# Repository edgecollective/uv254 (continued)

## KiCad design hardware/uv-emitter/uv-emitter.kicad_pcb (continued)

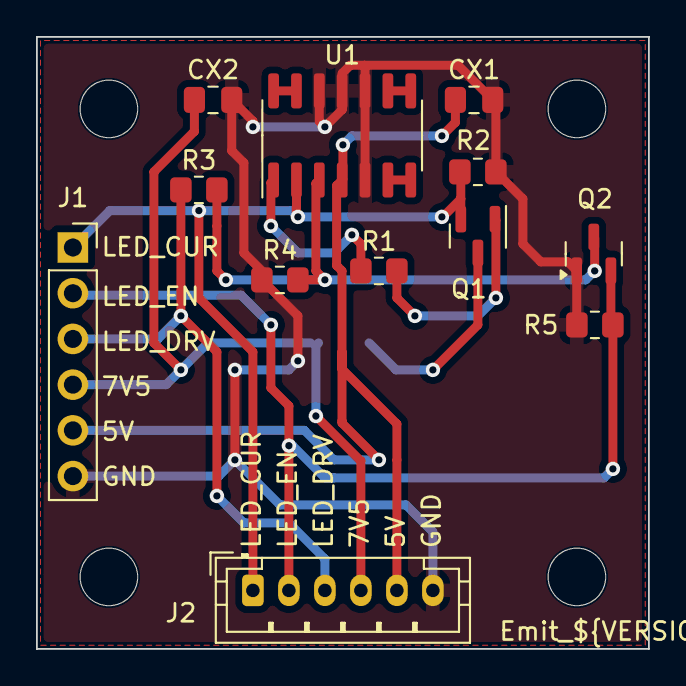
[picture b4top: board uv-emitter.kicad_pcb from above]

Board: 2 copper layers, 34.0 x 34.0 mm, 17 parts (1 on the bottom side), 13 nets.

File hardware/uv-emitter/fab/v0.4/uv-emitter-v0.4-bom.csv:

"Refs","Value","Footprint","Qty","DNP","Description"
"CX1","0.1 uF","Capacitor_SMD:C_0805_2012Metric_Pad1.18x1.45mm_HandSolder","1","","Unpolarized capacitor"
"CX2","1 uF","Capacitor_SMD:C_0805_2012Metric_Pad1.18x1.45mm_HandSolder","1","","Unpolarized capacitor"
"D1","UV LED","uv254:LED_IN-C35PPCTGU0","1","",""
"H1,H2,H3,H4","MountingHole","MountingHole:MountingHole_3.2mm_M3","4","","Mounting Hole without connection"
"J1","Conn_01x06_Socket","Connector_PinSocket_2.54mm:PinSocket_1x06_P2.54mm_Vertical","1","","Generic connector, single row, 01x06, script generated"
"J2","Conn_01x06_Socket","Connector_JST:JST_PH_B6B-PH-K_1x06_P2.00mm_Vertical","1","","Generic connector, single row, 01x06, script generated"
"Q1,Q2","2N7000","Package_TO_SOT_SMD:SOT-23","2","","0.2A Id, 200V Vds, N-Channel MOSFET, 2.6V Logic Level, TO-92"
"R1","49.9","Resistor_SMD:R_0805_2012Metric_Pad1.20x1.40mm_HandSolder","1","",""
"R2","24.9","Resistor_SMD:R_0805_2012Metric_Pad1.20x1.40mm_HandSolder","1","",""
"R3","100K","Resistor_SMD:R_0805_2012Metric_Pad1.20x1.40mm_HandSolder","1","",""
"R4","24.9K","Resistor_SMD:R_0805_2012Metric_Pad1.20x1.40mm_HandSolder","1","",""
"R5","10K","Resistor_SMD:R_0805_2012Metric_Pad1.20x1.40mm_HandSolder","1","",""
"U1","OPA4340UA","Package_SO:SOIC-14_3.9x8.7mm_P1.27mm","1","","Quad Single-Supply, Rail-to-Rail Operational Amplifier, MicroAmplifier Series, SOIC-14"

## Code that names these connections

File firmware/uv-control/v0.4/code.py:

# SPDX-License-Identifier: MIT
"""UV-Control v0.4 bring-up test.

Reads the detector and emitter signals through the ADS1115, switches the UV LED
and shows the readings on the ST7789 TFT and the USB serial console.

Board: SuperMini nRF52840 (CircuitPython's "SuperMini NRF52840" build).
Wiring: hardware/uv-control/v0.4-design.md (pin map).

Buttons:
  A  LED on/off (manual)
  B  measure: dark, LED on, dark again; shows light minus dark per channel
  C  use the last measurement as the blank, so later ones show absorbance
"""
import math
import time

import analogio
import board
import busio
import digitalio
import displayio
import terminalio
from adafruit_ads1x15 import ADS1115, AnalogIn, ads1x15
from adafruit_display_text import label
from adafruit_st7789 import ST7789
from fourwire import FourWire

# --- Pins: keep in step with the schematic and v0.4-design.md
TFT_SCK, TFT_MOSI, TFT_CS = board.P1_13, board.P0_10, board.P1_11
TFT_DC, TFT_RST, TFT_BL = board.P0_06, board.P0_08, board.P1_15
I2C_SDA, I2C_SCL = board.P0_17, board.P0_20
LED_ENABLE = board.P0_22   # emitter: HIGH forces the LED off, LOW lets LED_DRIVE set it
LED_DRIVE = board.P0_24    # emitter current setpoint: HIGH (3.3 V) gives about 26 mA
BOOST_EN = board.P1_00     # U1 (LMR62014) enable: HIGH turns the 8 V LED supply on
BUTTONS = (board.P0_11, board.P1_04, board.P1_06)   # A, B, C to GND
V8_SENSE = board.P0_31     # 8 V LED supply through a 20k/10k divider
DET_2V5 = board.P0_02      # the detector's 2.5 V reference

SENSE_OHMS = 24.9          # emitter current-sense resistor (R2 on the emitter)
SETTLE_S = 0.05            # wait after switching the LED before reading
SAMPLES = 8                # readings averaged per channel


def output(pin, value):
    io = digitalio.DigitalInOut(pin)
    io.switch_to_output(value=value)
    return io


# LED off before anything else
led_enable = output(LED_ENABLE, True)
led_drive = output(LED_DRIVE, False)
boost_en = output(BOOST_EN, True)
led_is_on = False


def set_led(on):
    global led_is_on
    led_drive.value = on
    led_enable.value = not on
    led_is_on = on


buttons = []
for pin in BUTTONS:
    b = digitalio.DigitalInOut(pin)
    b.switch_to_input(pull=digitalio.Pull.UP)
    buttons.append(b)
last_state = [True] * len(buttons)


def pressed():
    """Index of a button that was just pressed, or None."""
    for i, b in enumerate(buttons):
        down = not b.value
        if down and last_state[i]:
            last_state[i] = False
            return i
        if not down:
            last_state[i] = True
    return None


# --- ADC
i2c = busio.I2C(I2C_SCL, I2C_SDA)
ads = ADS1115(i2c)          # address 0x48 (ADDR to GND)
ads.gain = 1                # +/-4.096 V full scale
CHANNELS = (
    ("detect", AnalogIn(ads, ads1x15.Pin.A0)),
    ("rect", AnalogIn(ads, ads1x15.Pin.A1)),
    ("light-tight", AnalogIn(ads, ads1x15.Pin.A2)),
    ("LED sense", AnalogIn(ads, ads1x15.Pin.A3)),
)
v8 = analogio.AnalogIn(V8_SENSE)
v2v5 = analogio.AnalogIn(DET_2V5)


def read_all():
    sums = [0.0] * len(CHANNELS)
    for _ in range(SAMPLES):
        for i, (_, ch) in enumerate(CHANNELS):
            sums[i] += ch.voltage
    return [s / SAMPLES for s in sums]


def internal_volts(adc, scale=1.0):
    return adc.value / 65535 * adc.reference_voltage * scale


# --- Display: 2.0" 240x320 ST7789, used in landscape
displayio.release_displays()
spi = busio.SPI(TFT_SCK, MOSI=TFT_MOSI)
bus = FourWire(spi, command=TFT_DC, chip_select=TFT_CS, reset=TFT_RST, baudrate=24_000_000)
display = ST7789(bus, width=320, height=240, rotation=90, backlight_pin=TFT_BL)
screen = displayio.Group()
display.root_group = screen


def text_line(y, color=0xFFFFFF, scale=2):
    t = label.Label(terminalio.FONT, text="", color=color, scale=scale, x=6, y=y)
    screen.append(t)
    return t


title = text_line(12, 0x66CCFF)
title.text = "UV-Control v0.4"
rows = [text_line(44 + 24 * i) for i in range(len(CHANNELS))]
status = text_line(150, 0xFFCC00)
result = text_line(184, 0x99FF99)
hint = text_line(226, 0x888888, scale=1)
hint.text = "A: LED on/off   B: measure   C: set blank"

blank = None
last = None


def measure():
    """Light minus dark for each channel, with the LED off before and after."""
    set_led(False)
    time.sleep(SETTLE_S)
    dark1 = read_all()
    set_led(True)
    time.sleep(SETTLE_S)
    light = read_all()
    set_led(False)
    time.sleep(SETTLE_S)
    dark2 = read_all()
    return [l - (a + b) / 2 for l, a, b in zip(light, dark1, dark2)], light


print("time_s,detect_V,rect_V,light_tight_V,led_sense_V,led_on")
while True:
    button = pressed()
    if button == 0:
        set_led(not led_is_on)
    elif button == 1:
        last, light = measure()
        led_mA = light[3] / SENSE_OHMS * 1000
        line = "signal %.4f V  LED %.1f mA" % (last[0], led_mA)
        if blank and last[0] > 0 and blank[0] > 0:
            line = "A = %.4f  LED %.1f mA" % (-math.log10(last[0] / blank[0]), led_mA)
        result.text = line
        print("measure," + ",".join("%.5f" % v for v in last))
    elif button == 2 and last:
        blank = last
        result.text = "blank set: %.4f V" % blank[0]

    volts = read_all()
    for row, (name, _), v in zip(rows, CHANNELS, volts):
        row.text = "%-11s %7.4f V" % (name, v)
    status.text = "LED %s  8V %.2f V  2V5 %.3f V" % (
        "ON " if led_is_on else "off", internal_volts(v8, 3.0), internal_volts(v2v5))
    print("%.2f,%s,%d" % (time.monotonic(), ",".join("%.5f" % v for v in volts), led_is_on))
    time.sleep(0.2)
